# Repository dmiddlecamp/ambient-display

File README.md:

ambient-display
===============

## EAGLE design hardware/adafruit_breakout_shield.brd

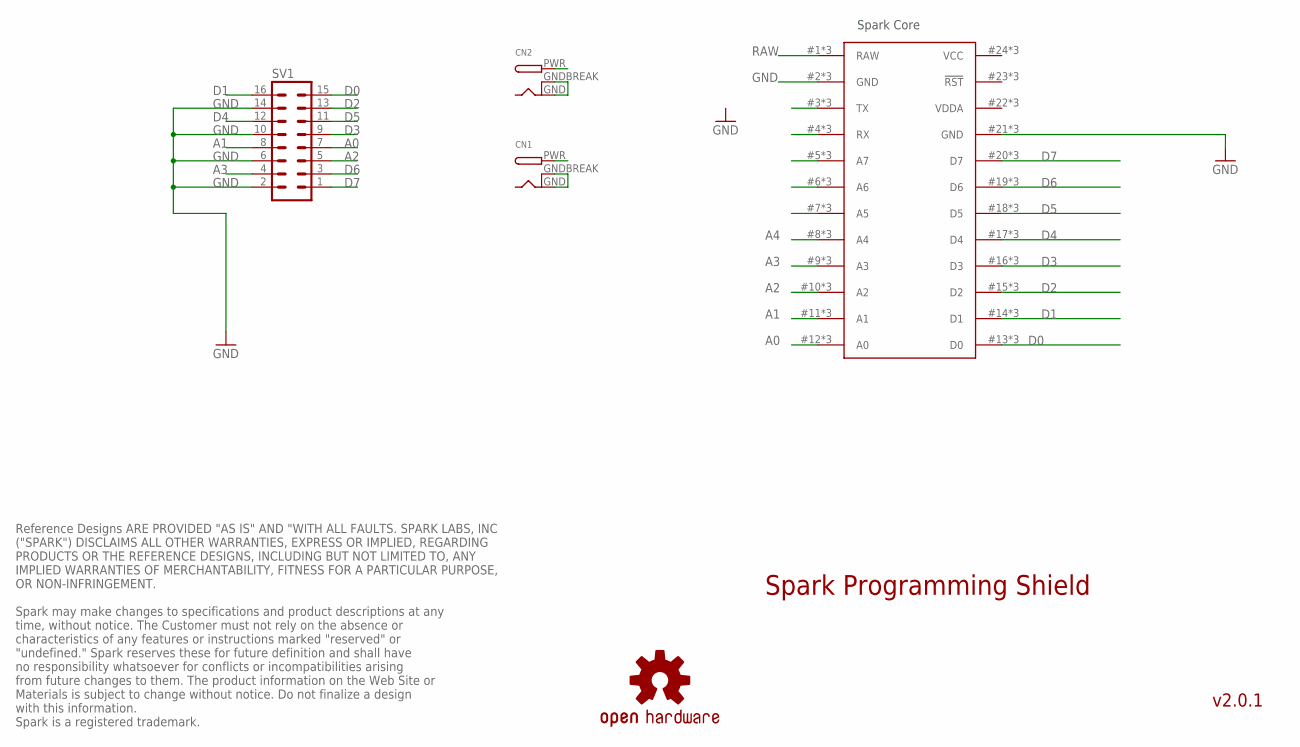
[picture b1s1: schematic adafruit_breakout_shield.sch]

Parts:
CN1, CN2: DCBARRELPTH; DCJACK_2MM_PTH
LOGO1: OSHW-LOGOM; OSHW-LOGO-M
SV1: ML16
U$1: SPARK_CORE; SPARK_CORE_STACKABLE

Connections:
A0: SV1.7, U$1.12 (A0), U$1.#12 (A0), U$1.@12 (A0)
A1: SV1.8, U$1.11 (A1), U$1.#11 (A1), U$1.@11 (A1)
A2: SV1.5, U$1.10 (A2), U$1.#10 (A2), U$1.@10 (A2)
A3: SV1.4, U$1.9 (A3), U$1.#9 (A3), U$1.@9 (A3)
A4: U$1.8 (A4), U$1.#8 (A4), U$1.@8 (A4)
D0: SV1.15, U$1.13 (D0), U$1.#13 (D0), U$1.@13 (D0)
D1: SV1.16, U$1.14 (D1), U$1.#14 (D1), U$1.@14 (D1)
D2: SV1.13, U$1.15 (D2), U$1.#15 (D2), U$1.@15 (D2)
D3: SV1.9, U$1.16 (D3), U$1.#16 (D3), U$1.@16 (D3)
D4: SV1.12, U$1.17 (D4), U$1.#17 (D4), U$1.@17 (D4)
D5: SV1.11, U$1.18 (D5), U$1.#18 (D5), U$1.@18 (D5)
D6: SV1.3, U$1.19 (D6), U$1.#19 (D6), U$1.@19 (D6)
D7: SV1.1, U$1.20 (D7), U$1.#20 (D7), U$1.@20 (D7)
GND: CN1.GND, CN1.GNDBREAK, CN2.GND, CN2.GNDBREAK, SV1.2, SV1.6, SV1.10, SV1.14, U$1.2 (GND), U$1.21 (GND), U$1.#2 (GND), U$1.#21 (GND), U$1.@2 (GND), U$1.@21 (GND)
unnamed: U$1.7 (A5), U$1.#7 (A5), U$1.@7 (A5)
unnamed: U$1.6 (A6), U$1.#6 (A6), U$1.@6 (A6)
unnamed: U$1.5 (A7), U$1.#5 (A7), U$1.@5 (A7)
unnamed: U$1.4 (RX), U$1.#4 (RX), U$1.@4 (RX)
unnamed: U$1.3 (TX), U$1.#3 (TX), U$1.@3 (TX)
RAW: CN1.PWR, CN2.PWR, U$1.1 (RAW), U$1.#1 (RAW), U$1.@1 (RAW)
VCC: U$1.24 (VCC), U$1.#24 (VCC), U$1.@24 (VCC)
VDDA: U$1.22 (VDDA), U$1.#22 (VDDA), U$1.@22 (VDDA)

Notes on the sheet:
Spark Core
Spark Programming Shield
v2.0.1
Reference Designs ARE PROVIDED "AS IS" AND "WITH ALL FAULTS. SPARK LABS, INC ("SPARK") DISCLAIMS ALL OTHER WARRANTIES, EXPRESS OR IMPLIED, REGARDING PRODUCTS OR THE REFERENCE DESIGNS, INCLUDING BUT NOT LIMITED TO, ANY IMPLIED WARRANTIES OF MERCHANTABILITY, FITNESS FOR A PARTICULAR PURPOSE, OR NON-I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

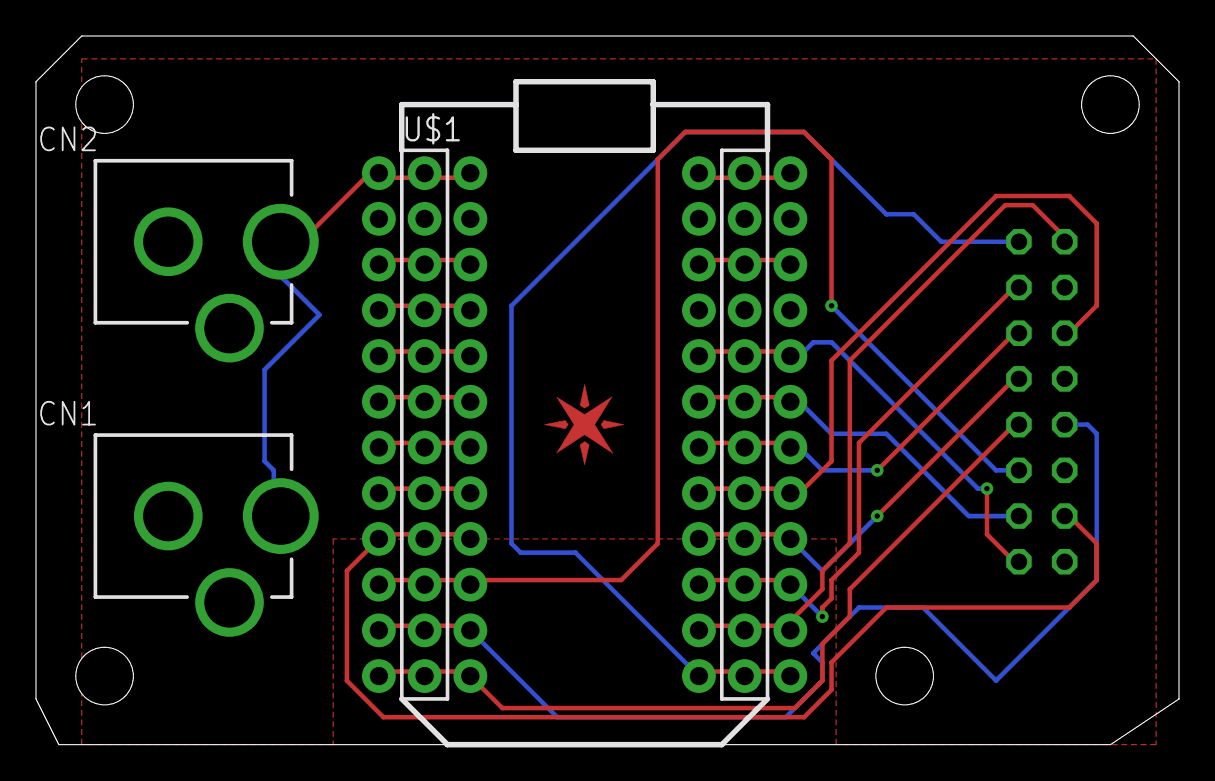
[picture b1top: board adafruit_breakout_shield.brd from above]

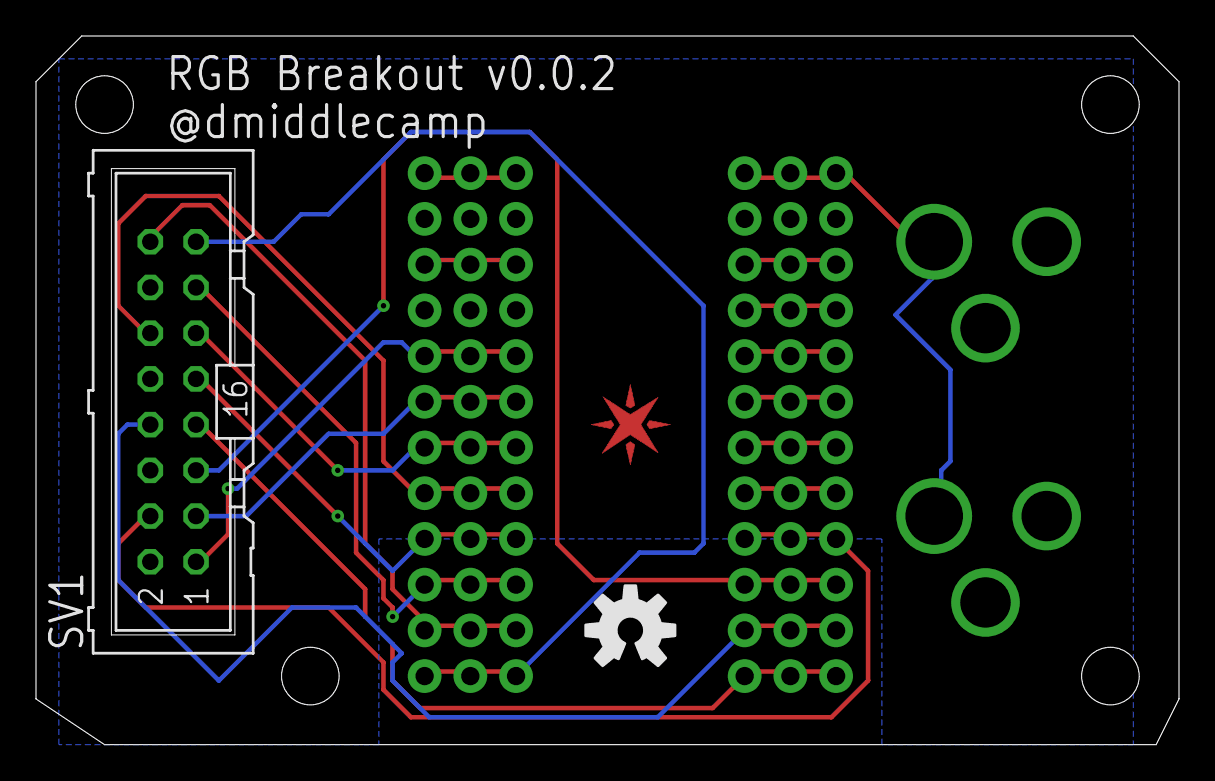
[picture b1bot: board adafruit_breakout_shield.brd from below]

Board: 2 copper layers, 63.5 x 39.4 mm, 6 parts (2 on the bottom side), 22 nets.

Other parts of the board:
E$1: SPARK_LOGO_PLUS_PLANE

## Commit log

2014-08-07 ignore
2014-08-07 remove modules
2014-08-07 proc
2014-08-07 reducing delay for presentation
2014-08-07 heroku settings
2014-08-07 init
2014-08-07 trying this again
2014-08-07 trying this
2014-08-07 fixes
2014-08-07 removing
2014-08-07 firmware
2014-08-07 notes
2014-08-07 boards
2014-09-01 initial
2014-09-03 okay, coordinate system seems to be working, but colors are off.
2014-10-04 32x32 color tester
2014-10-04 ball tosser!
